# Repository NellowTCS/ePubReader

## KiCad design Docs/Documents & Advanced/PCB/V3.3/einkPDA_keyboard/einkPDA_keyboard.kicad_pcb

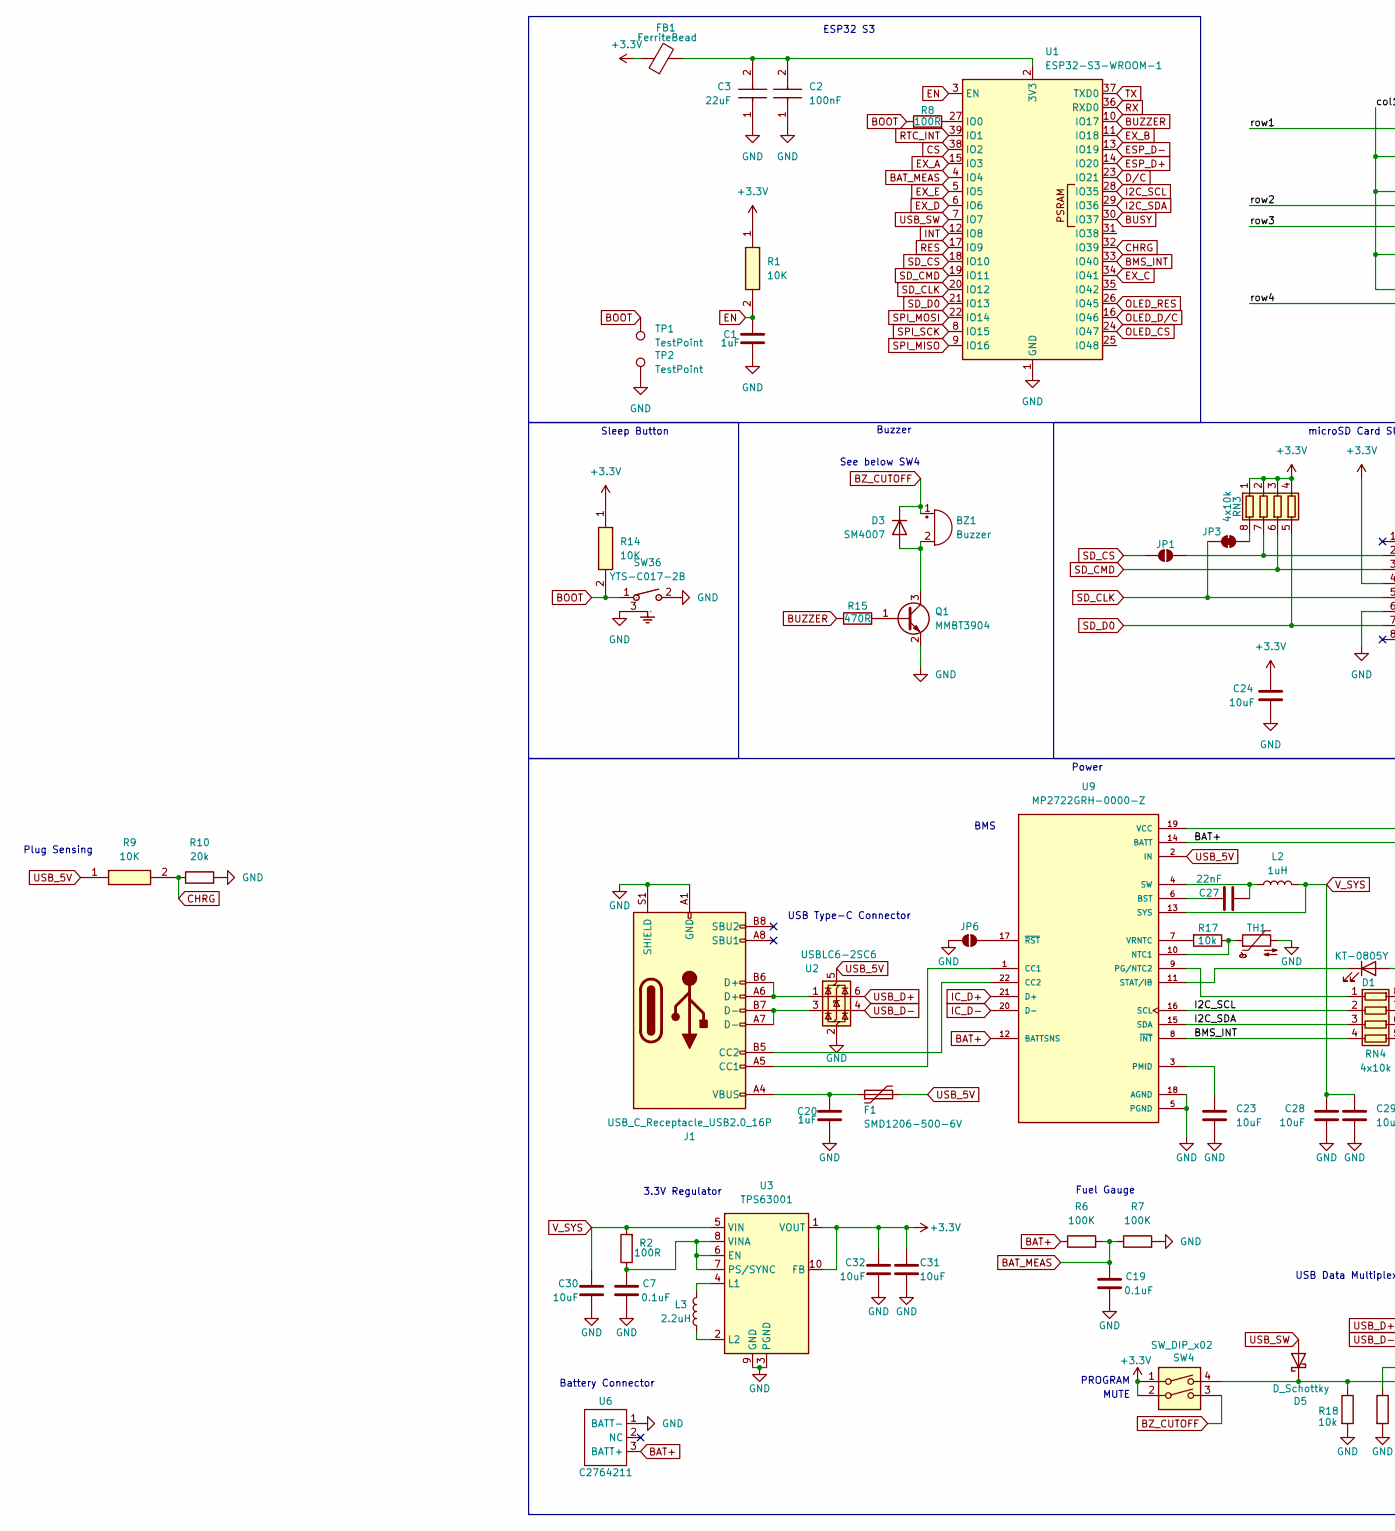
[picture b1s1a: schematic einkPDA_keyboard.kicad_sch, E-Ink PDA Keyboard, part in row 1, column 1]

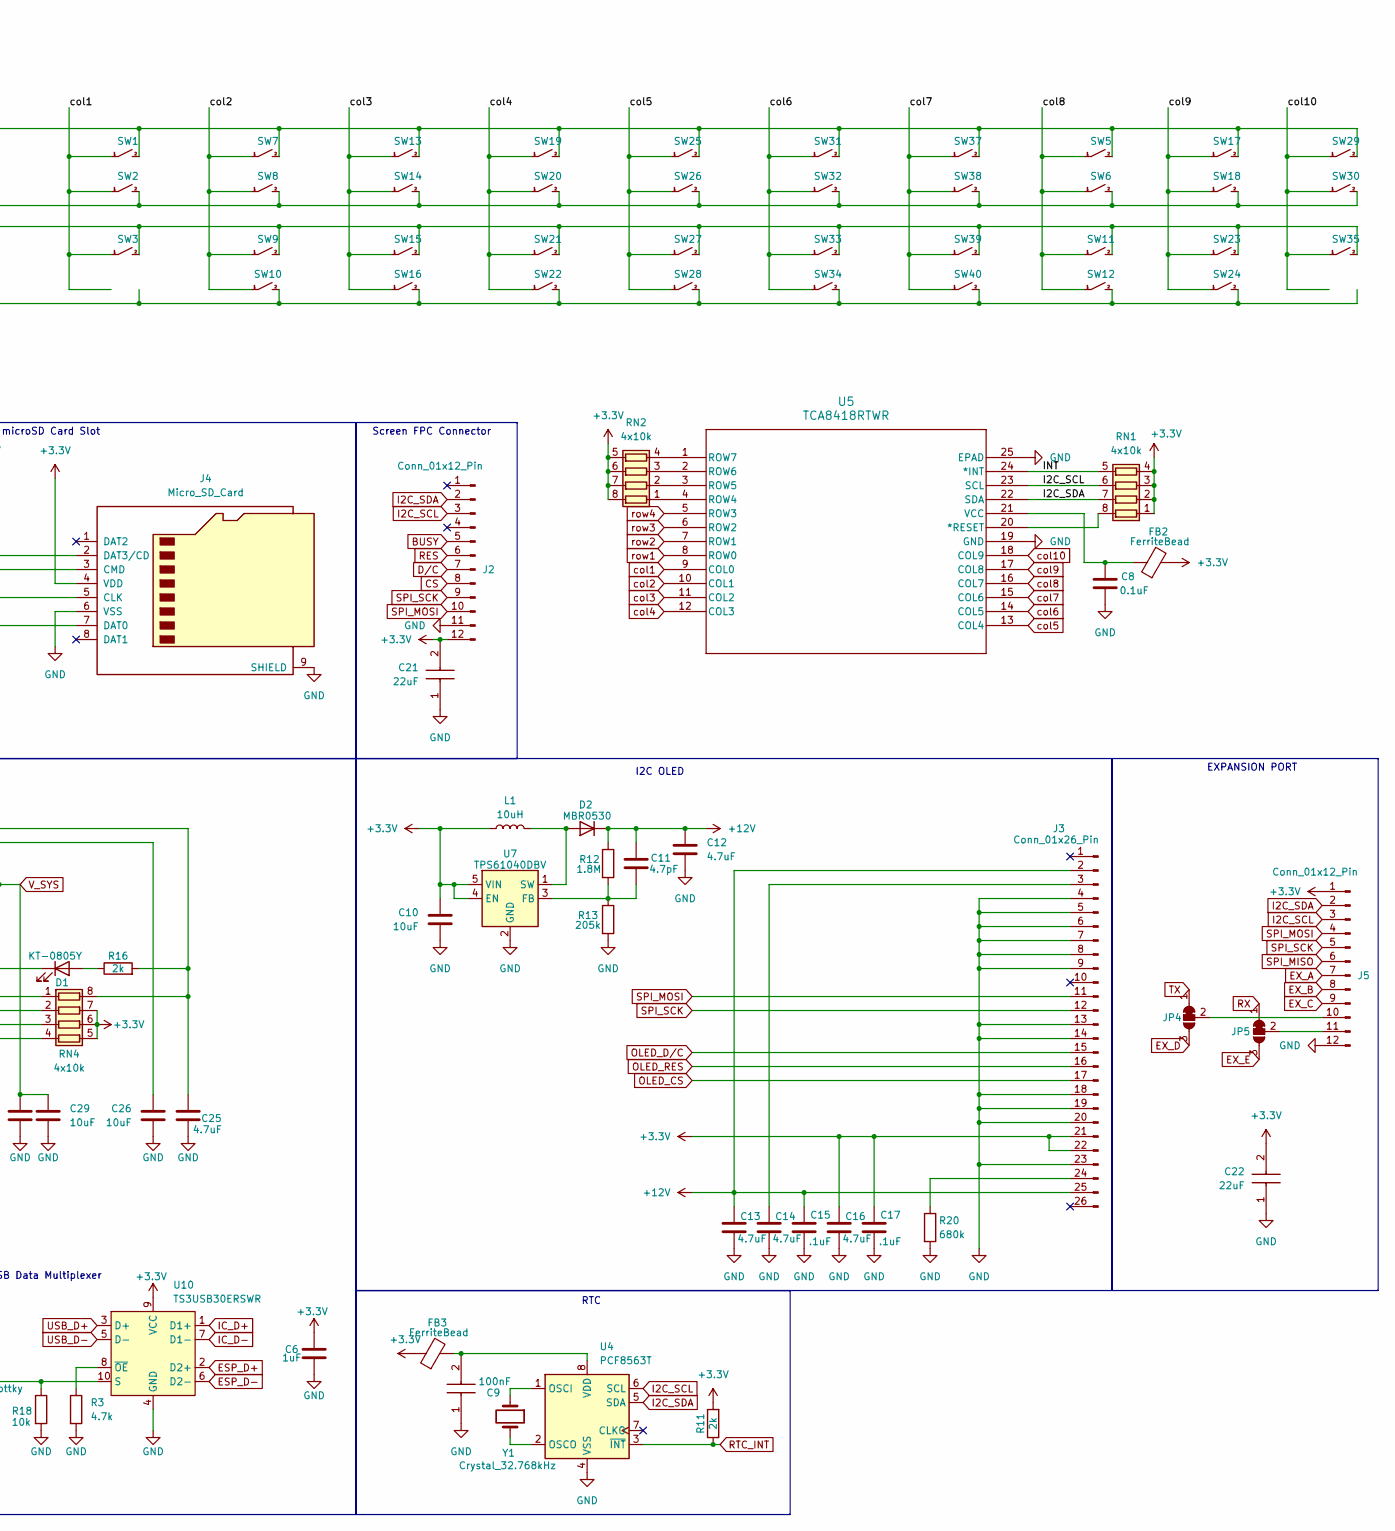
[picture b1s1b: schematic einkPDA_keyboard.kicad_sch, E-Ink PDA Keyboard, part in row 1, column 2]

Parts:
BZ1: Buzzer; BUZ-SMD_3P_L5.0-W5.0-P3.50-TL; LCSC Part # C781883
C1, C6, C20: 1uF; C_0603_1608Metric; LCSC Part # C15849
C2, C9: 100nF; C_0805_2012Metric; Mouser Part Number 603-CC805KRX7R9BB104
C3, C21, C22: 22uF; C_0805_2012Metric; Mouser Part Number 187-CL21A226MAQNNNE
C7, C8, C19: 0.1uF; C_0402_1005Metric; LCSC Part # C1525
C10, C23, C26, C28, C29, C30, C31, C32: 10uF; C_0805_2012Metric; LCSC PART # C15850
C11: 4.7pF; C_0603_1608Metric; LCSC PART # C1669
C12, C13, C14, C16: 4.7uF; C_1206_3216Metric; LCSC PART # C29823
C15, C17: .1uF; C_0805_2012Metric; LCSC PART # C28233
C24: 10uF; C_0805_2012Metric; LCSC Part # C15850
C25: 4.7uF; C_0805_2012Metric; LCSC Part # C1779
C27: 22nF; C_0603_1608Metric; LCSC Part # C21122
D1: KT-0805Y; LED_0805_2012Metric; LCSC Part # C2296
D2: MBR0530; D_SOD-123; LCSC PART # C77336
D3: SM4007; D_SOD-123F; LCSC Part # C64898
D5: D_Schottky; D_SOD-323; LCSC Part # C191023
F1: SMD1206-500-6V; Fuse_1206_3216Metric; LCSC Part # C2760308
FB1, FB2, FB3: FerriteBead; L_0603_1608Metric; LCSC Part # C85831
J1: USB_C_Receptacle_USB2.0_16P; USB-TYPE-C-SMD_TYPE-C-16P-QTWT; LCSC Part # C5187472
J2, J5: Conn_01x12_Pin; AFC01-S12FCA-00; LCSC Part # C262661
J3: Conn_01x26_Pin; FPC-SMD_AFC24-S26FIA [DUAL-SIDE]; LCSC PART # C262684
J4: Micro_SD_Card; TF-SMD_503398-1892; LCSC Part # C428492
JP1, JP6: SolderJumper_2_Open; SolderJumper-2_P1.3mm_Open_RoundedPad1.0x1.5mm
JP3: SolderJumper_2_Bridged; SolderJumper-2_P1.3mm_Bridged_RoundedPad1.0x1.5mm
JP4, JP5: SolderJumper_3_Bridged12; SolderJumper-3_P1.3mm_Bridged12_RoundedPad1.0x1.5mm
L1: 10uH; L_Chilisin_BMRx00060630; LCSC PART # C5189958
L2: 1uH; L_Ferrocore_DLG-0504; LCSC Part # C2929426
L3: 2.2uH; L_Wurth_WE-LQSH-3012; LCSC Part # C19734
Q1: MMBT3904; SOT-23; LCSC Part # C20526
R1, R9, R14: 10K; R_0805_2012Metric; Mouser Part Number 303-0805W8F1002T5E
R2, R8: 100R; R_0603_1608Metric; LCSC Part # C22775
R3: 4.7k; R_0603_1608Metric; LCSC Part # C23162
R6, R7: 100K; R_0603_1608Metric; LCSC Part # C25803
R10: 20k; R_0603_1608Metric; LCSC Part # C4184
R11, R16: 2k; R_0805_2012Metric; LCSC Part # C17604
R12: 1.8M; R_0805_2012Metric; LCSC PART # C17399
R13: 205k; R_0805_2012Metric; LCSC PART # C218417
R15: 470R; R_0805_2012Metric; LCSC Part # C17710
R17: 10k; R_0805_2012Metric; LCSC Part # C17414
R18: 10k; R_0603_1608Metric; LCSC Part # C25804
R20: 680k; R_0805_2012Metric; LCSC PART # C17797
RN1, RN2, RN3, RN4: 4x10k; R_Array_Concave_4x0603; LCSC Part # C29718
SW1, SW2, SW3, SW5, SW6, SW7, SW8, SW9, SW10, SW11, SW12, SW13, SW14, SW15, SW16, SW17, SW18, SW19, SW20, SW21, SW22, SW23, SW24, SW25, SW26, SW27, SW28, SW29, SW30, SW31, SW32, SW33, SW34, SW35, SW37, SW38, SW39, SW40: contact_pad_SINGLE
SW4: SW_DIP_x02; 2X_DIP_DHN-02-V-TR; LCSC Part # C224995
SW36: YTS-C017-2B; KEY-TH_3P-L4.5-W4.5-P3.0-EH; Manufacturer Part YTS-C017-2B
TH1: NTC; R_0603_1608Metric; LCSC Part # C76589
TP1, TP2: TestPoint; TestPoint_Pad_1.0x1.0mm
U1: ESP32-S3-WROOM-1; LCSC Part # C2913202
U2: USBLC6-2SC6; SOT-23-6; LCSC Part # C7519
U3: TPS63001; Texas_DRC0010J_ThermalVias; LCSC Part # C28060
U4: PCF8563T; SOIC-8_3.9x4.9mm_P1.27mm; LCSC Part # C7440
U5: TCA8418RTWR; RTW24_2P45X2P45; LCSC Part # C138713
U6: C2764211; JST_PH_2P_P2.00mm; LCSC Part # C2764211
U7: TPS61040DBV; SOT-23-5; LCSC PART # C7722
U9: MP2722GRH-0000-Z; IC_MP2722GRH-0000-Z; PARTREV 1.0; LCSC Part # C20099551
U10: TS3USB30ERSWR; UQFN-10_1.4x1.8mm_P0.4mm; LCSC Part # C73880
Y1: Crystal_32.768kHz; Crystal_SMD_3215-2Pin_3.2x1.5mm; LCSC Part # C5213671

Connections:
+3.3V: C6.2, C10.2, C16.1, C17.1, C21.2, C22.2, C24.1, C31.2, C32.2, FB1.1, FB2.2, FB3.1, J2.12, J3.21, J3.22, J4.4 (VDD), J5.1, L1.1, R1.1, R11.2, R14.1, RN1.1 (R1.1), RN1.2 (R2.1), RN1.3 (R3.1), RN1.4 (R4.1), RN2.5 (R4.2), RN2.6 (R3.2), RN2.7 (R2.2), RN2.8 (R1.2), RN3.1 (R1.1), RN3.2 (R2.1), RN3.3 (R3.1), RN3.4 (R4.1), RN4.5 (R4.2), RN4.6 (R3.2), RN4.7 (R2.2), SW4.1, SW4.2, U3.1 (VOUT), U3.10 (FB), U7.4 (EN), U7.5 (VIN), U10.9 (VCC)
+12V: C11.2, C12.1, C13.1, C15.1, D2.1 (K), J3.2, J3.25, R12.1
BAT+: C26.2, R6.1, U6.3 (BATT+), U9.12 (BATTSNS), U9.14 (BATT)
BAT_MEAS: C19.1, R6.2, R7.1, U1.4 (IO4)
BMS_INT: RN4.4 (R4.1), U1.33 (IO40), U9.8 (~INT)
BOOT: R8.1, R14.2, SW36.1, TP1.1
BUSY: J2.5, U1.30 (IO37)
BUZZER: R15.1, U1.10 (IO17)
BZ_CUTOFF: BZ1.1 (+), D3.1 (K), SW4.3
CHRG: R9.2, R10.1, U1.32 (IO39)
CS: J2.8, U1.38 (IO2)
D/C: J2.7, U1.23 (IO21)
EN: C1.2, R1.2, U1.3 (EN)
ESP_D+: U1.14 (IO20), U10.2 (D2+)
ESP_D-: U1.13 (IO19), U10.6 (D2-)
EX_A: J5.7, U1.15 (IO3)
EX_B: J5.8, U1.11 (IO18)
EX_C: J5.9, U1.34 (IO41)
EX_D: JP4.3 (B), U1.6 (IO6)
EX_E: JP5.3 (B), U1.5 (IO5)
GND: C1.1, C2.1, C3.1, C6.1, C7.2, C8.2, C9.1, C10.1, C12.2, C13.2, C14.2, C15.2, C16.2, C17.2, C19.2, C20.1, C21.1, C22.1, C23.1, C24.2, C25.2, C26.1, C28.1, C29.1, C30.1, C31.1, C32.1, J1.A1 (GND), J1.A12 (GND), J1.B1 (GND), J1.B12 (GND), J1.S1 (SHIELD), J2.11, J3.4, J3.5, J3.6, J3.7, J3.8, J3.9, J3.13, J3.14, J3.18, J3.19, J3.20, J3.23, J4.6 (VSS), J4.9 (SHIELD), J5.12, JP6.1 (A), Q1.2 (E), R3.2, R7.2, R10.2, R13.2, R18.2, R20.2, SW36.2, SW36.3 (GND), TH1.2, TP2.1, U1.1 (GND), U1.40 (GND), U1.41 (GND), U2.2 (GND), U3.3 (PGND), U3.9 (GND), U3.11 (PGND), U4.4 (VSS), U5.19 (GND), U5.25 (EPAD), U6.1 (BATT-), U7.2 (GND), U9.5 (PGND), U9.18 (AGND), U10.4 (GND); also elsewhere on the board
I2C_SCL: J2.3, J5.3, RN1.6 (R3.2), RN4.2 (R2.1), U1.28 (IO35), U4.6 (SCL), U5.23 (SCL), U9.16 (SCL)
I2C_SDA: J2.2, J5.2, RN1.7 (R2.2), RN4.3 (R3.1), U1.29 (IO36), U4.5 (SDA), U5.22 (SDA), U9.15 (SDA)
IC_D+: U9.21 (D+), U10.1 (D1+)
IC_D-: U9.20 (D-), U10.7 (D1-)
INT: RN1.5 (R4.2), U1.12 (IO8), U5.24 (*INT)
unnamed: BZ1.2 (-), D3.2 (A), Q1.3 (C)
unnamed: C20.2, F1.1, J1.A4 (VBUS), J1.A9 (VBUS), J1.B4 (VBUS), J1.B9 (VBUS)
unnamed: D1.2 (A), R16.1
unnamed: D1.1 (K), U9.11 (STAT/IB)
unnamed: D2.2 (A), L1.2, U7.1 (SW)
unnamed: D5.1 (K), R18.1, SW4.4, U10.10 (S)
unnamed: J1.A5 (CC1), U9.1 (CC1)
unnamed: J1.B5 (CC2), U9.22 (CC2)
unnamed: J1.A6 (D+), J1.B6 (D+), U2.1 (I/O1)
unnamed: J1.A7 (D-), J1.B7 (D-), U2.3 (I/O2)
unnamed: C14.1, J3.3
unnamed: J3.24, R20.1
unnamed: J4.2 (DAT3/CD), JP1.2 (B), RN3.7 (R2.2)
unnamed: J5.10, JP4.2 (C)
unnamed: J5.11, JP5.2 (C)
unnamed: JP3.2 (B), RN3.8 (R1.2)
unnamed: JP6.2 (B), U9.17 (~RST)
unnamed: Q1.1 (B), R15.2
unnamed: RN1.8 (R1.2), U5.20 (*RESET)
unnamed: RN2.1 (R1.1), U5.4 (ROW4)
unnamed: RN2.2 (R2.1), U5.3 (ROW5)
unnamed: RN2.3 (R3.1), U5.2 (ROW6)
unnamed: RN2.4 (R4.1), U5.1 (ROW7)
unnamed: RN4.1 (R1.1), U9.9 (PG/NTC2)
unnamed: C25.1, R16.2, RN4.8 (R1.2), U9.19 (VCC)
unnamed: C2.2, C3.2, FB1.2, U1.2 (3V3)
unnamed: R8.2, U1.27 (IO0)
unnamed: C7.1, R2.1, U3.6 (EN), U3.7 (PS/SYNC), U3.8 (VINA)
unnamed: L3.1, U3.4 (L1)
unnamed: L3.2, U3.2 (L2)
unnamed: U4.1 (OSCI), Y1.1
unnamed: U4.2 (OSCO), Y1.2
unnamed: C9.2, FB3.2, U4.8 (VDD)
unnamed: C8.1, FB2.1, U5.21 (VCC)
unnamed: C11.1, R12.2, R13.1, U7.3 (FB)
unnamed: C27.2, U9.6 (BST)
unnamed: R17.1, TH1.1, U9.10 (NTC1)
unnamed: C23.2, U9.3 (PMID)
unnamed: C27.1, L2.1, U9.4 (SW)
unnamed: R17.2, U9.7 (VRNTC)
unnamed: R3.1, U10.8 (~OE)
OLED_CS: J3.17, U1.24 (IO47)
OLED_D/C: J3.15, U1.16 (IO46)
OLED_RES: J3.16, U1.26 (IO45)
RES: J2.6, U1.17 (IO9)
RTC_INT: R11.1, U1.39 (IO1), U4.3 (~INT)
RX: JP5.1 (A), U1.36 (RXD0)
SD_CLK: J4.5 (CLK), JP3.1 (A), U1.20 (IO12)
SD_CMD: J4.3 (CMD), RN3.6 (R3.2), U1.19 (IO11)
SD_CS: JP1.1 (A), U1.18 (IO10)
SD_D0: J4.7 (DAT0), RN3.5 (R4.2), U1.21 (IO13)
SPI_MISO: J5.6, U1.9 (IO16)
SPI_MOSI: J2.10, J3.11, J5.4, U1.22 (IO14)
SPI_SCK: J2.9, J3.12, J5.5, U1.8 (IO15)
TX: JP4.1 (A), U1.37 (TXD0)
USB_5V: F1.2, R9.1, U2.5 (VBUS), U9.2 (IN)
USB_D+: U2.6 (I/O1), U10.3 (D+)
USB_D-: U2.4 (I/O2), U10.5 (D-)
USB_SW: D5.2 (A), U1.7 (IO7)
V_SYS: C28.2, C29.2, C30.2, L2.2, R2.2, U3.5 (VIN), U9.13 (SYS)
col1: SW1.1, SW2.1, SW3.1, U5.9 (COL0)
col2: SW7.1, SW8.1, SW9.1, SW10.1, U5.10 (COL1)
col3: SW13.1, SW14.1, SW15.1, SW16.1, U5.11 (COL2)
col4: SW19.1, SW20.1, SW21.1, SW22.1, U5.12 (COL3)
col5: SW25.1, SW26.1, SW27.1, SW28.1, U5.13 (COL4)
col6: SW31.1, SW32.1, SW33.1, SW34.1, U5.14 (COL5)
col7: SW37.1, SW38.1, SW39.1, SW40.1, U5.15 (COL6)
col8: SW5.1, SW6.1, SW11.1, SW12.1, U5.16 (COL7)
col9: SW17.1, SW18.1, SW23.1, SW24.1, U5.17 (COL8)
col10: SW29.1, SW30.1, SW35.1, U5.18 (COL9)
row1: SW1.2, SW5.2, SW7.2, SW13.2, SW17.2, SW19.2, SW25.2, SW29.2, SW31.2, SW37.2, U5.8 (ROW0)
row2: SW2.2, SW6.2, SW8.2, SW14.2, SW18.2, SW20.2, SW26.2, SW30.2, SW32.2, SW38.2, U5.7 (ROW1)
row3: SW3.2, SW9.2, SW11.2, SW15.2, SW21.2, SW23.2, SW27.2, SW33.2, SW35.2, SW39.2, U5.6 (ROW2)
row4: SW10.2, SW12.2, SW16.2, SW22.2, SW24.2, SW28.2, SW34.2, SW40.2, U5.5 (ROW3)

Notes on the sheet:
Plug Sensing
ESP32 S3
RTC
Screen FPC Connector
PROGRAM
Buzzer
Battery Connector
See below SW4
Power
microSD Card Slot
Fuel Gauge
USB Data Multiplexer
USB Type-C Connector
3.3V Regulator
EXPANSION PORT
Sleep Button
MUTE
BMS
I2C OLED

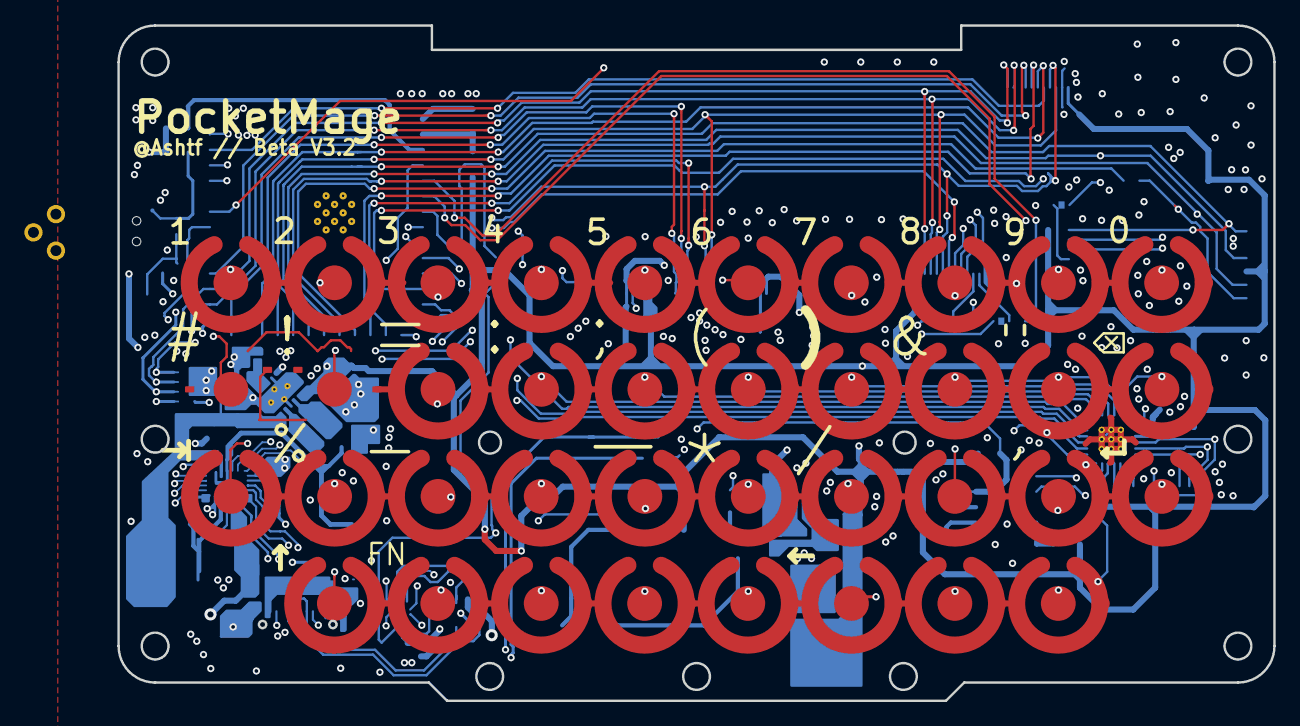
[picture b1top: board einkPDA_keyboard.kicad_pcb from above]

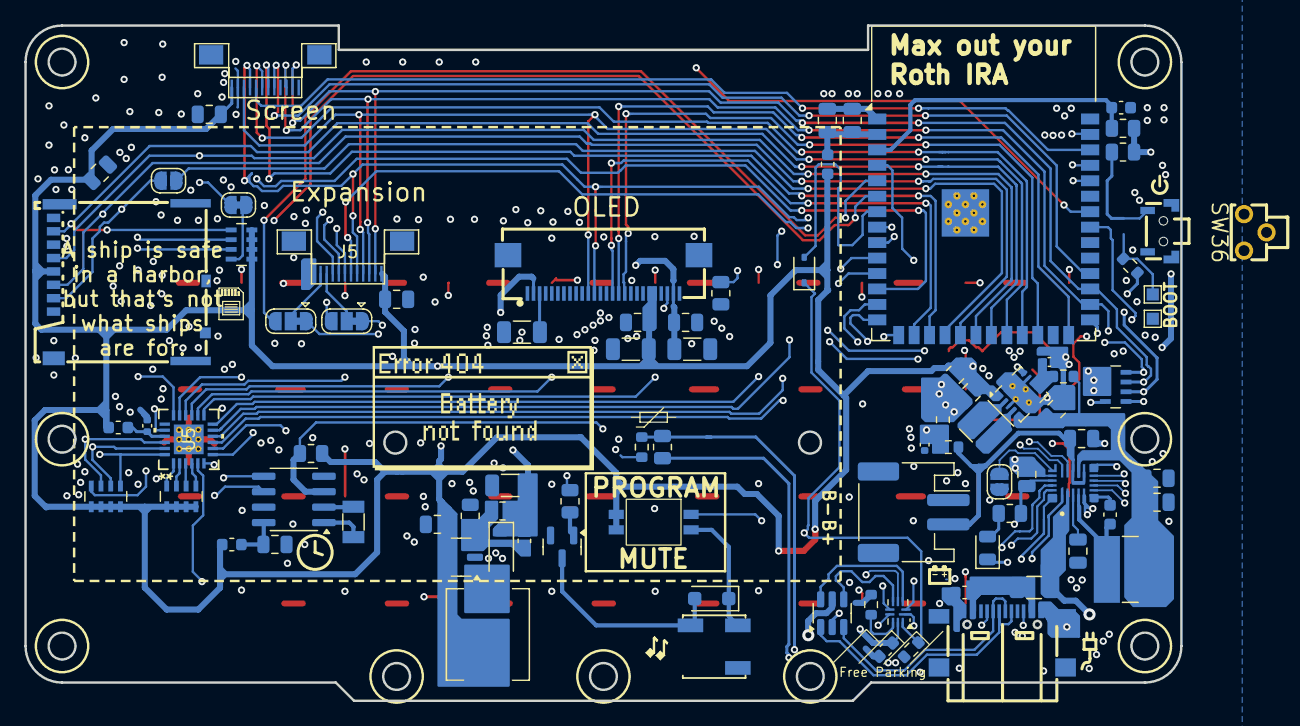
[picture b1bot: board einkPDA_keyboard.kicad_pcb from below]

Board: 4 copper layers, 95.0 x 55.5 mm, 125 parts (87 on the bottom side), 99 nets.

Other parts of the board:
SW43: EVQPUL02K; SW-SMD_TS24CA

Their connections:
GND: SW43.4; also elsewhere on the board

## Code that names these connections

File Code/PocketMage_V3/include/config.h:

#ifndef CONFIG_H
#define CONFIG_H

// OTA App
// Is this an OTA APP? // OTA_APP: set -DOTA_APP_FLAG=1 in platformio.ini
#if OTA_APP_FLAG
#define OTA_APP true
#else
#define OTA_APP false
#endif

// CONFIGURATION & SETTINGS
////////////////////////////////////////////////////////////////////////////////////////////////////////////////////////////|
#define KB_COOLDOWN 3                           // Keypress cooldown
#define MAX_FILES 10                            // Number of files to store
#define FORMAT_SPIFFS_IF_FAILED true            // Format the SPIFFS filesystem if mount fails
#define SLEEPMODE "TEXT"                        // TEXT, SPLASH, CLOCK
#define TXT_APP_STYLE 1                         // 0: Old Style (NOT SUPPORTED), 1: New Style
#define SET_CLOCK_ON_UPLOAD false               // Should system clock be set automatically on code upload?
#define TOUCH_TIMEOUT_MS 1200                   // Delay after scrolling to return to typing mode (ms)
#define SYS_METADATA_FILE "/sys/SDMMC_META.txt" // File path to the file system metadata file
#define POWER_SAVE_FREQ 40                      // CPU freq for power save mode
#define IDLE_TIME 20000                         // time to wait for mage idle (ms)

// Full refresh after N partial refreshes (CHANGE WITH CAUTION)
#if POCKETMAGE_HW_VERSION == 2
  #define FULL_REFRESH_AFTER 10 // Prod uses N=10                    
#else
  #define FULL_REFRESH_AFTER 5  // Beta needs N=5
#endif
////////////////////////////////////////////////////////////////////////////////////////////////////////////////////////////|

// PIN DEFINITION
#define I2C_SCL       35
#define I2C_SDA       36
#define MPR121_ADDR   0x5A
#define MP2722_ADDR   0x3F
#define USB_MUX_PIN   7

#define KB_IRQ        8
#define PWR_BTN       0 
#define BAT_SENS      4
#define CHRG_SENS     39
#define RTC_INT       1 
#define LOAD_SWITCH   38

// SPI
#define SPI_MOSI      14
#define SPI_SCK       15

// OLED
#define OLED_CS       47
#define OLED_DC       46
#define OLED_RST      45

// E Ink
#define EPD_CS        2
#define EPD_DC        21
#define EPD_RST       9
#define EPD_BUSY      37

// SDMMC mode
#define SD_CLK        12
#define SD_CMD        11
#define SD_D0         13
#define SD_D1         5
#define SD_D2         6
#define SD_D3         10

// SDSPI mode
#define SD_CS         10
#define SD_MOSI       11
#define SD_SCK        12
#define SD_MISO       13

#define BZ_PIN        17

// ===================== SYSTEM SETTINGS =====================
// Persistent preferences
extern int TIMEOUT;              // Auto sleep timeout (seconds)
extern bool DEBUG_VERBOSE;       // Extra debug output
extern bool SYSTEM_CLOCK;        // Show clock on screen
extern bool SHOW_YEAR;           // Show year in clock
extern bool SAVE_POWER;          // Enable power saving mode
extern bool ALLOW_NO_MICROSD;    // Allow running without SD card
extern bool HOME_ON_BOOT;        // Start home app on boot
extern int OLED_BRIGHTNESS;      // OLED brightness (0-255)
extern int OLED_MAX_FPS;         // OLED max FPS
extern bool SD_SPI_COMPATIBILITY;

#endif

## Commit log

2026-02-16 WIP PCB updates
2026-03-05 Update PCB
2026-03-30 Add hint for failure case
2026-03-31 Attempted USB patch
2026-04-08 Keyboard softlock patch 2
2026-04-08 WIP - Implement hardware versioning
2026-04-09 Update PCBs
2026-04-09 Refactor firmware build workflow with release support
    Refactor GitHub Actions workflow for firmware build and deployment. Added support for release events, improved steps for artifact handling, and enhanced manifest generation.
2026-04-13 Enhance firmware build for Beta and Production
    Updated firmware build process to include Beta and Production environments, and created separate manifest files for each environment.
2026-04-13 Refactor firmware URL handling in index.html
2026-04-16 refactor sleep logic
2026-04-16 WIP implement repeat code input UI
2026-04-19 Polish GUI
2026-04-21 Update Mesh-NOW version
2026-04-21 Add Potion Functions
    ## Inputs (Keyboard & Touch)
    getKey() – Polls the hardware keyboard buffer and returns the ASCII integer value of the pressed key (or 0 if none).
    getTouch() – Returns the directional scroll vector (-1, 0, or 1) from the capacitive touch slider.
    waitForKeypress(message) – Halts script execution and displays a full-screen blocking message on the OLED until a hardware key is pressed.
    ## UI Prompts (OLED)
    prompt(message) – Triggers the native text-entry UI and returns the user's typed string.
2026-04-23 WIP chat app UI
2026-04-23 Add workflow_dispatch trigger to publish-docs.yml
2026-04-23 Update links for CAD and dictionary files in FAQ
2026-04-27 Update fullPotionCommandList with new examples
2026-04-27 Add scrolling to terminal WIP
2026-05-02 Better color coding on netflags
2026-05-02 Update PCB with new changes
2026-05-03 Add scrollbar to TXT
2026-05-03 Fix visual bug with long lines getting cut off in small font mode
2026-05-05 PCB updates
2026-05-05 fix submodules
2026-06-14 Crashing attempt 1
2026-06-15 Fixes and improvements
2026-06-15 There
2026-06-15 Yeah never mind I'm making a reader for Honzo
2026-06-16 Hehe
2026-06-16 Move
2026-06-16 HONZO TIMEEEEEEEE
2026-06-16 Add build
2026-06-16 Cursor based
2026-06-16 Metadata!
2026-06-16 UI fixes
2026-06-16 Update tar build
2026-06-17 chore: auto-build HonzoReader.tar
2026-06-17 Fix submodule mess: remove stale Mesh-NOW gitlink at wrong path, deduplicate .gitmodules U8g2 entry
2026-06-17 Replace Font Headers with U8g2
2026-06-17 So many fixes
2026-06-17 Font Selector and GOTO Line command
2026-06-17 Docs Update
2026-06-21 Fix battery state not updating
2026-06-28 Keyboard PCB Update
